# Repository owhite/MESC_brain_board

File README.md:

# Balancing Robot Design and Implementation

This repository is a structured set of lab notes and implementation records for developing a two-wheeled self-balancing robot. It documents the workflows from physical modeling and parameter measurement through firmware design, control implementation, and experimental validation.

The focus is on reproducibility and engineering rigor: measured motor parameters, deterministic control-loop behavior, system identification, control design tradeoffs, and verification testing are all captured alongside working code and experiments.

Topics covered include:
- Control design and validation workflows for balancing robots
- Motor parameter measurement (phase resistance, d/q inductance, damping)
- Deterministic embedded firmware structure for real-time control
- Encoder integration and signal integrity checks
- CAN communication and timing behavior
- Failure modes and debugging notes
- Practical test methods and instrumentation results

These notes are intended to make the development and validation process transparent and repeatable, not just to present final code.

## My balancing robot journey, specs and testing

* A subset of steps required to get a robot to stand [[LINK](DOCS/balancing_checklist.md)]
* Common issues that can break balancing in the brain board project [[LINK](DOCS/balancing_failures.md)]
* Firmware design choices that keep the balancing control loop deterministic [[LINK](DOCS/determinism_design.md)]
* Measuring phase resistance, d-axis, and q-axis inductance of a BLDC Motor [[LINK](DOCS/BLDC_inductance_measurement.md)]
* Dial in ChatGPT to be skeptical lab partner: [[LINK](DOCS/chatGPT_tips.md)]
* Development of the robot control board [[LINK](brainboardV1.2/README.md)]
* OTA programming [[LINK](RPI_OTA_BRIDGE/README.md)]
* Finalizing the modeling workflow [[LINK](modeling/README.md)]

## Not totally coherent discussions:
* [LQR](DOCS/learn_LQR.md). 
* Using the MT6701 [[LINK](DOCS/MT6701.md)] → works great but required some minor modifications to MESC position and [velocity measurement](DOCS/pos_vel_CAN.md)
* Measuring jitter on the MESC [[LINK](DOCS/jitter_testing.md)] → none found at current operating speeds
* Implementing CAN [[LINK](DOCS/CAN.md)]
* Notes about MESC [[LINK](DOCS/MESC_control_variables.md)]
* The inadequacies of PID [[LINK](DOCS/PID_position.md)]. 
* General description of firmware: [LINK](DOCS/teensy_firmware_walkthrough.md). 
* Brain board firmware [[LINK](DOCS/software_specs.md)]

## Laboratory notes, 2025

* [Position hold](DOCS/sept12_position_hold.md)
* [Controller issues](DOCS/sept18_controller_issues.md)
* [Torque nonlinearity](DOCS/sept19_torque_nonlinearity.md)
* [PID notes](DOCS/sept23_PID_notes.md)
* [Least squares](DOCS/sept30_least_squares.md)
* [Torque response](DOCS/oct03_torque_response.md)
* [LQR modeling](DOCS/oct11_LQR_modeling.md)
* [LQR height](DOCS/oct12_LQR_height.md)
* [IMU testing](DOCS/nov16_IMU.md)

## Let's be real

**You probably will not want to hear this.** If you came here for the code to make a balancing robot, it is here, but it probably wont help. 

You might assume building a balancing robot is mostly a matter of assembling parts and flashing someone else’s code onto it. I used to think that too — until I finally worked out how to create on one. Balancing robots are not just bolted together -- they are tuned and integrated. Everything about them depends on tight interactions between hardware, sensors, motors, and feedback loops, and those interactions are different for every single robot.

A balancing robot is a dynamic control system, not a static device. It’s constantly trying to predict its own motion, measure its own tilt, compensate for delays, cancel vibration, and stabilize itself against gravity — hundreds of times per second. That means even small differences in hardware completely change the way the controller behaves. For example:

- Motors & ESCs: Different torque curves, different dead zones, different current limits, different FOC tuning.
- Wheels & tires: Diameter, traction, inertia, compliance — all change how the robot responds to torque.
- IMU: Sensitivity, noise, mounting vibration, sample timing, bias drift — all affect measured tilt.
- Microcontroller timing: Loop rate, jitter, scheduling delays, filter performance — all shift the controller behavior.
- Physical build: Height of the center of mass, frame stiffness, mass distribution — all change the robot’s dynamics.

If you change any of these, even slightly, the controller behaves differently. That’s why tuning is so time-consuming: you’re adjusting a control law to match the physics and imperfections of your specific robot.

_You are welcome to take my code and run it on your bot._ But unfortunately just like musical instruments or high-performance cars, balancing robots need to be customized, adjusted, and dialed in until the system “feels right.” The code is just the beginning; the tuning is the craft.

Why? Well:
- Your robot will not balance without a lot of tuning.
- What's most important to use this project as a prompt for making your own system
- Tuning is the real work — not a flaw, but part of the fun
- What really makes a robot stand is eliminating all the problems like jitter, timing issues, CAN communications, and modeling

**Finally, dearest reader**... I care about you, youre adorable, but quite unfortunately one the PCB for one of the ESCs that I use is closed source. Nothing would delight me more to make it open and I will try. For a while, I was using the Flipsky Mini FSESC6.7 pro 70A but I got tired of blowing them up because of cheap parts. Some day I will make a balancing bot that runs on [moteus](https://mjbots.com/products/moteus-r4-11) or [odrive](https://odriverobotics.com) but right now that is not a priority. 

For these reasons and others you cant expect to use this repo to build a balancing robot like some sort of kit.

## The really great news is there is a new source of help. 

I want to be transparent about this: building a robot is not about writing code. I've written code for 20 plus years, in my case I worked through the entire project with ChatGPT as a kind of engineering partner. ChatG helps with asking questions, testing ideas, refining approaches, debugging weird behavior, and iterating the design over and over.

A balancing robot is a complex closed-loop control problem. As far as I know I never would have been able to use Google to address how robots behaves. ChatGPT creates the ability to explore those problems conversationally:

- When I wasn’t sure whether the IMU filtering was right, I asked it to analyze my data.
- It is incredible at helping with plotting results
- When I had motor vibration I couldn’t explain, I used chat to brainstorm possible causes and experiments.
- It taught me everything about LQR, interpretted equations, supplied python code to perform most of the calculations. It involved a lot of debugging -- when the LQR gains seemed wrong, I walked through the math with it.
- When the ESC behavior looked inconsistent, we debugged line by line until we understood it.
- When I needed to test an assumption, it helped me design the test.
- When something behaved strangely, I could describe it and get three possible hypotheses to try.
- ChatG is uncanny at image analysis. It reads part numbers off of chips and will take you to the spec sheet. Take a picture of a square wave of your scope - - the damn thing will tell you the frequency, amplitude of the wave. It also taught me how to set up [one-shot measurements](DOCS/BLDC_inductance_measurement.md). 

The project was far less like copying code from the internet and more like having a very patient senior engineer building one-off code bundles to eventually get this thing to stand. 

**We live in a world of prompt-driven engineering:** I shaped my thinking through prompts, refined those prompts based on the robot’s behavior, and used those conversations to build understanding that would have taken months on my own. ChatGPT didn’t “solve the problem” — it helped me reason through it, step by step.

So if you see this robot standing and balancing in a video, know that behind the scenes was not just hardware and code — it was hundreds of micro-conversations, experiments, adjustments, and iterations. ChatGPT was the scaffolding that helped me structure that process.

## ACKNOWLEDGEMENTS
This project would be completely impossible without the help, support and guidance of David Molony, developer of [MESC firmware](https://github.com/davidmolony/MESC_Firmware.git). Use of the MESC firmware is described throughout this repo.

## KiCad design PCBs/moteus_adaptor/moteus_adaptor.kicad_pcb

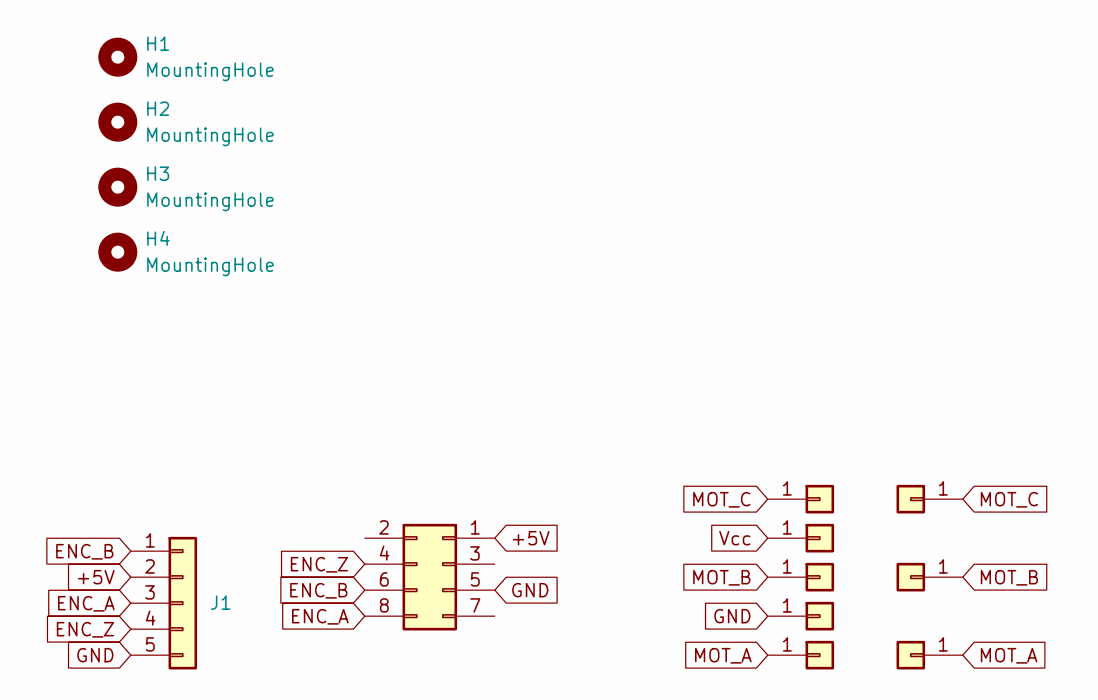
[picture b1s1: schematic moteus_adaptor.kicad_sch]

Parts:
H1, H2, H3, H4: MountingHole; MountingHole_2.5mm
J1: Conn_01x05; PinHeader_1x05_P2.54mm_Vertical
J2: Conn_02x04_Odd_Even; PinSocket_2x04_P1.27mm_Vertical
J3, J4, J5, J6, J7: Conn_01x01; my_Pin_D2.0mm
J8, J10, J12: Conn_01x01; my_Pin_D2.6mm

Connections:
+5V: J1.2, J2.1
ENC_A: J1.3, J2.8
ENC_B: J1.1, J2.6
ENC_Z: J1.4, J2.4
GND: J1.5, J2.5, J5.1
MOT_A: J6.1, J12.1
MOT_B: J4.1, J10.1
MOT_C: J7.1, J8.1
Vcc: J3.1

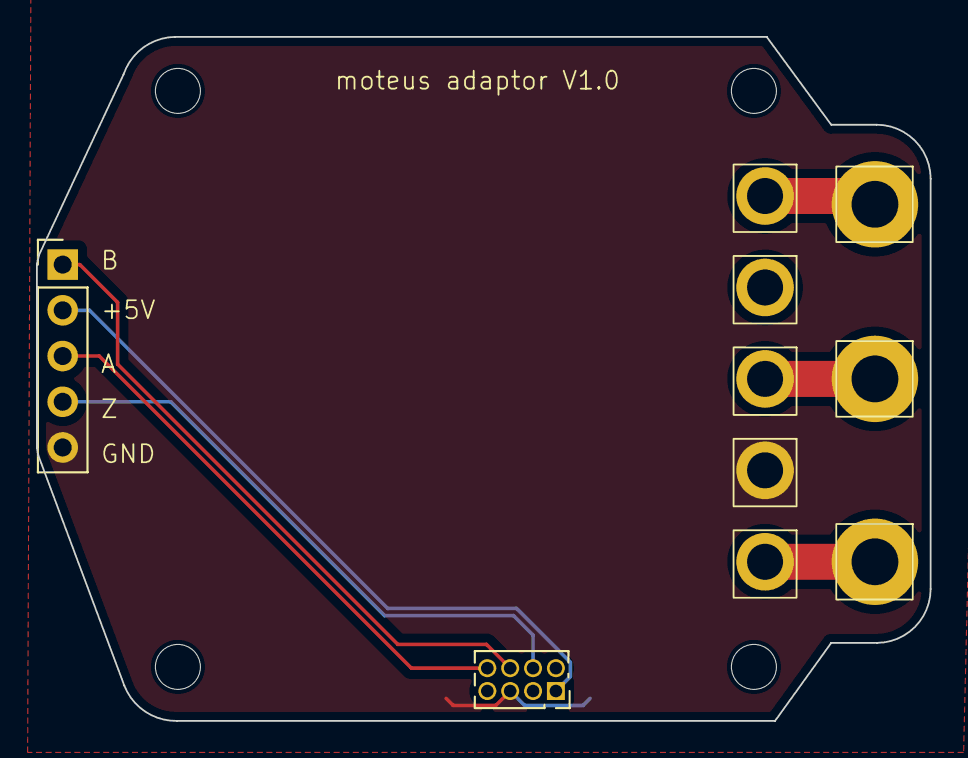
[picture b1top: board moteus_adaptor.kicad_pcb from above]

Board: 2 copper layers, 49.7 x 38.0 mm, 14 parts (0 on the bottom side), 8 nets.

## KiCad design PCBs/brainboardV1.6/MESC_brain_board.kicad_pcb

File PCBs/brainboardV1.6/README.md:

# MESC BRAIN BOARD 

A PCB and software development project for a balancing robot. 

The goal is to use a hobby Electronic Speed Controller (one open source [example](https://github.com/owhite/MP2-DFN), and this circuit for a [brain board](https://github.com/owhite/MESC_brain_board/blob/main/brainboardV1.0/MESC_brain_board.pdf), a teensy 4.0, and an ESP-32, in combination with [MESC firmware](https://github.com/davidmolony/MESC_Firmware).

## GENERAL APPROACH

A separation of concerns is divided across these architectures:

* **Teensy:** Runs the high-level brain → gait generator, balance estimator, RC inputs
* **MESC:** The firmware on the ESC for control → torque or velocity loops per joint
* **ESP32:** Easy to log and analyze later → pumps UDP to the computer
* **Desktop computer** → perfectly adequate way of viewing high speed data with UDP

## TEENSY 4.0
* 600+ MHz ARM Cortex-M7 — plenty of headroom for filtering, control loops, gait logic, telemetry
* Tons of I/O for IMU, encoders, RC input, WiFi (via ESP add-on), etc.
* Precise timing with elapsedMicros or interrupts for deterministic control
* Great for real-time control, sensor fusion, and behavior modeling

## MESC MOTOR CONTROLLER
* Deploys on simple DIY or commercially available ESC boards
* Executes low-level Field-Oriented Control (FOC) motor control 
* Built-in support for encoders, FOC, and torque estimation
* Accurate low-level motor control using current sensing
* Reads angular position from the MT6701 encoder via SPI or PWM
* UART/CAN interface (RX + TX)	Real-time communication with the Teensy
* PWM / FOC commutation w/ efficient, smooth motor operation

## OTHER BRAIN BOARD FEATURES
* RC receiver connector (for PWM/PPM/SBUS input)
* ESP32 UART serial programmer
* Power input connector
* Voltage divider (to monitor battery voltage)
* Push-button E-stop connector
* Power button (for system on/off)
* IMU connector (e.g., MPU-6050)
* Buzzer (for system alerts or E-stop signal)
* MESC I/O
* Reserved 2 GPIO pins on Teensy for emergency shutoff to MESC
* CAN connector (for MESC motor control)

## CAN BUS
* Full-duplex communication between Teensy and motor controllers
* Carries:
  * Commands: set_torque, set_velocity, enable_motor, zero_encoder, etc.
  * Telemetry: encoder position, estimated torque, velocity, fault codes
* Real-time performance with minimal latency
* Can support multiple motor controllers on the same bus

## MANY THANKS
This project would never happen without:
* [MESC firmware](https://github.com/davidmolony/MESC_Firmware). 
* [Netzpfuscher's](https://github.com/Netzpfuscher/TTerm) incredible TTerm and CAN work.
* [MP2](https://github.com/badgineer/MP2-ESC) an open source motor controller from badgineer. 

## NOTES
Ever wanted to change all the names of kicad files at once?

use this:
```
python3 replace_kicad_names.py VESC_brain_board MESC_brain_board
```

[[LINK](replace_kicad_names.py)]

## STILL NEEDS WORK
* Not great design w/ DC-DC conversion from high voltage VBat
* Replace out the IMU for a ICM-42688-P
* Order / revise pushbuttons for programming the ESP32
* Ensure 3.3V CAN transciever

## VERSIONS
* See github tag [pcb-v1](https://github.com/owhite/MESC_brain_board/releases/tag/pcb-v1) for V1.0
* Retreive with this command: "git checkout pcb-v1"

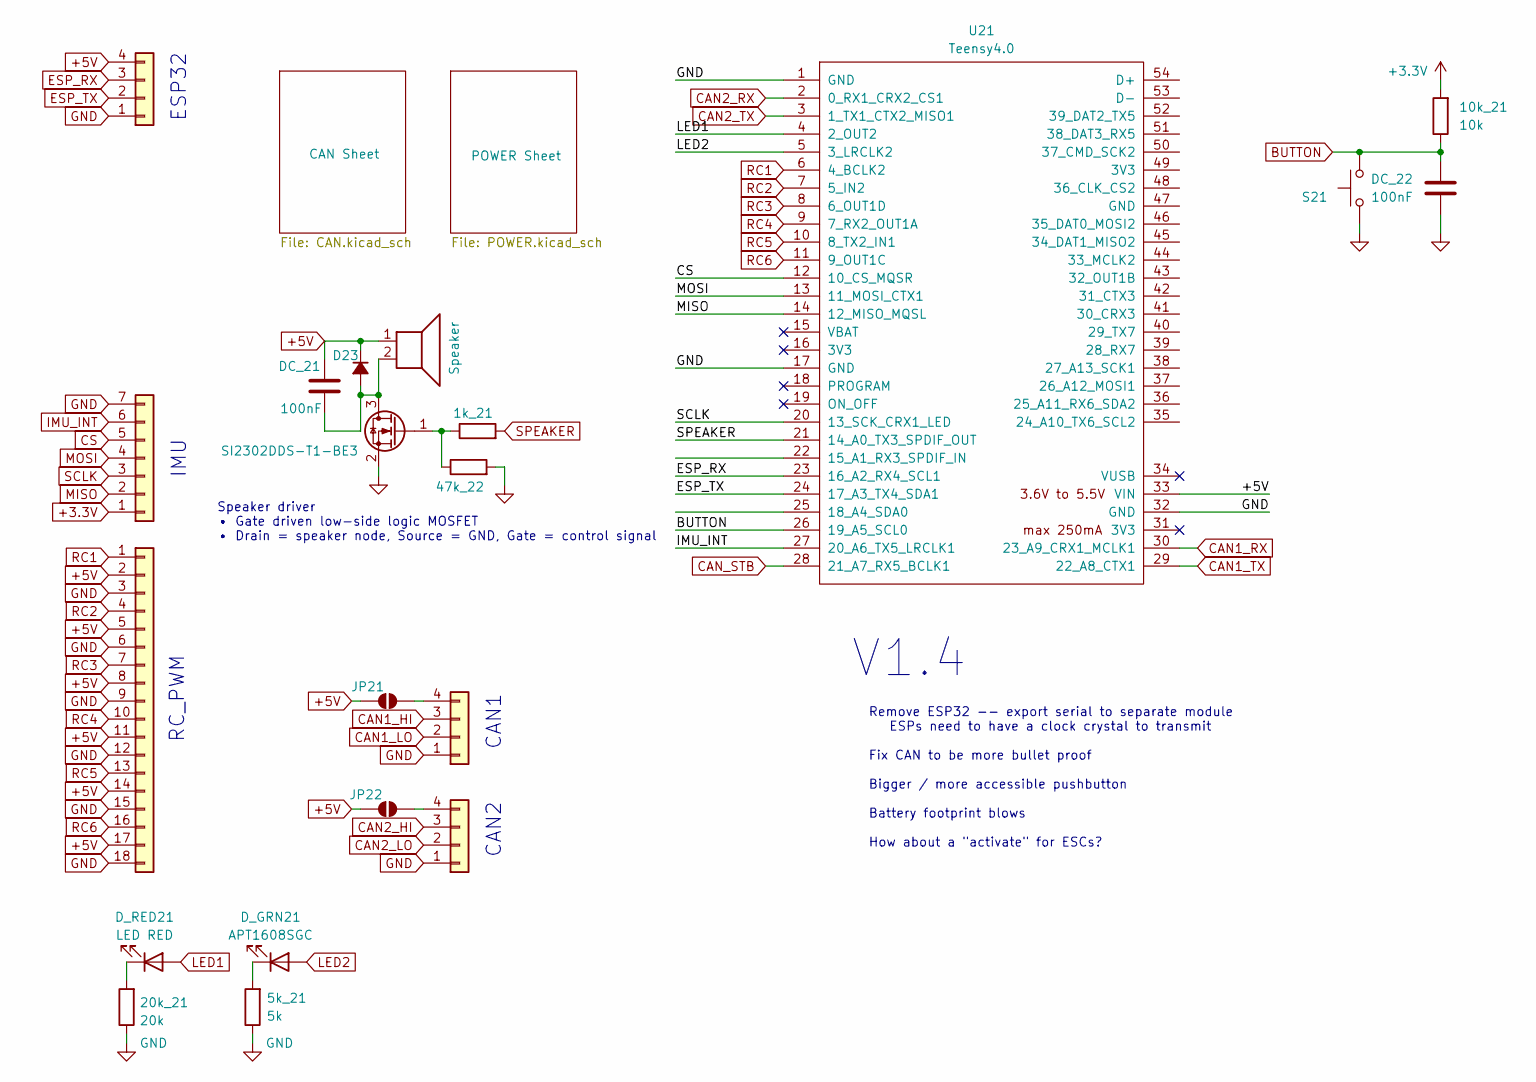
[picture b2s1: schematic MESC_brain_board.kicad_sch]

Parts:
1k_21, 47k_22: 10k; R_0603_1608Metric
5k_21: 5k; R_0603_1608Metric; LCSC C4184
10k_21: 10k; R_0603_1608Metric; LCSC C25804
20k_21: 20k; R_0603_1608Metric; LCSC C4184
CAN1, CAN2: Conn_01x04; JST_PH_B4B-PH-K_1x04_P2.00mm_Vertical
D23: D_Small_Filled; D_SMA
DC_21: 100nF; C_0603_1608Metric
DC_22: 100nF; C_0603_1608Metric; LCSC C14663
D_GRN21: APT1608SGC; LED_0603_1608Metric; LCSC APT1608SGC
D_RED21: LED RED; LED_0603_1608Metric; LCSC APT1608SURCK
ESP1: Conn_01x04; JST_PH_B4B-PH-K_1x04_P2.00mm_Vertical
IMU1: Conn_01x07; JST_PH_B7B-PH-K_1x07_P2.00mm_Vertical
J2: Conn_01x18; my_PinSocket_3x07_P2.54mm_Vertical
JP21, JP22: SolderJumper_2_Open; SolderJumper-2_P1.3mm_Open_RoundedPad1.0x1.5mm
LS21: Speaker; SPKR_CDS-13138-SMT-TR
Q21: SI2302DDS-T1-BE3; SOT-23
S21: TL1015AF160QG; SW_Push_SPST_NO_Alps_SKRK
U21: Teensy4.0; Teensy40

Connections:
+3.3V: 10k_21.2, IMU1.1; also elsewhere on the board
+5V: D23.1 (K), DC_21.1, ESP1.4, J2.2, J2.5, J2.8, J2.11, J2.14, J2.17, JP21.1 (A), JP22.1 (A), LS21.1, U21.33 (VIN); also elsewhere on the board
BUTTON: 10k_21.1, DC_22.2, S21.2, U21.26 (19_A5_SCL0)
CAN1_HI: CAN1.3; also elsewhere on the board
CAN1_LO: CAN1.2; also elsewhere on the board
CAN1_RX: U21.30 (23_A9_CRX1_MCLK1); also elsewhere on the board
CAN1_TX: U21.29 (22_A8_CTX1); also elsewhere on the board
CAN2_HI: CAN2.3; also elsewhere on the board
CAN2_LO: CAN2.2; also elsewhere on the board
CAN2_RX: U21.2 (0_RX1_CRX2_CS1); also elsewhere on the board
CAN2_TX: U21.3 (1_TX1_CTX2_MISO1); also elsewhere on the board
CAN_STB: U21.28 (21_A7_RX5_BCLK1); also elsewhere on the board
CS: IMU1.5, U21.12 (10_CS_MQSR)
ESP_RX: ESP1.3, U21.23 (16_A2_RX4_SCL1)
ESP_TX: ESP1.2, U21.24 (17_A3_TX4_SDA1)
GND: 5k_21.1, 20k_21.1, 47k_22.2, CAN1.1, CAN2.1, DC_22.1, ESP1.1, IMU1.7, J2.3, J2.6, J2.9, J2.12, J2.15, J2.18, Q21.2 (S), S21.1, U21.1 (GND), U21.17 (GND), U21.32 (GND); also elsewhere on the board
IMU_INT: IMU1.6, U21.27 (20_A6_TX5_LRCLK1)
LED1: D_RED21.2 (A), U21.4 (2_OUT2)
LED2: D_GRN21.2 (A), U21.5 (3_LRCLK2)
MISO: IMU1.2, U21.14 (12_MISO_MQSL)
MOSI: IMU1.4, U21.13 (11_MOSI_CTX1)
unnamed: CAN1.4, JP21.2 (B)
unnamed: CAN2.4, JP22.2 (B)
unnamed: D23.2 (A), DC_21.2, LS21.2, Q21.3 (D)
unnamed: 5k_21.2, D_GRN21.1 (K)
unnamed: 20k_21.2, D_RED21.1 (K)
unnamed: 1k_21.1, 47k_22.1, Q21.1 (G)
RC1: J2.1, U21.6 (4_BCLK2)
RC2: J2.4, U21.7 (5_IN2)
RC3: J2.7, U21.8 (6_OUT1D)
RC4: J2.10, U21.9 (7_RX2_OUT1A)
RC5: J2.13, U21.10 (8_TX2_IN1)
RC6: J2.16, U21.11 (9_OUT1C)
SCLK: IMU1.3, U21.20 (13_SCK_CRX1_LED)
SPEAKER: 1k_21.2, U21.21 (14_A0_TX3_SPDIF_OUT)

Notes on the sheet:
CAN2
IMU
V1.4
RC_PWM
Remove ESP32 -- export serial to separate module ESPs need to have a clock crystal to transmit Fix CAN to be more bullet proof Bigger / more accessible pushbutton Battery footprint blows How about a "activate" for ESCs?
Speaker driver • Gate driven low-side logic MOSFET • Drain = speaker node, Source = GND, Gate = control signal
CAN1
ESP32

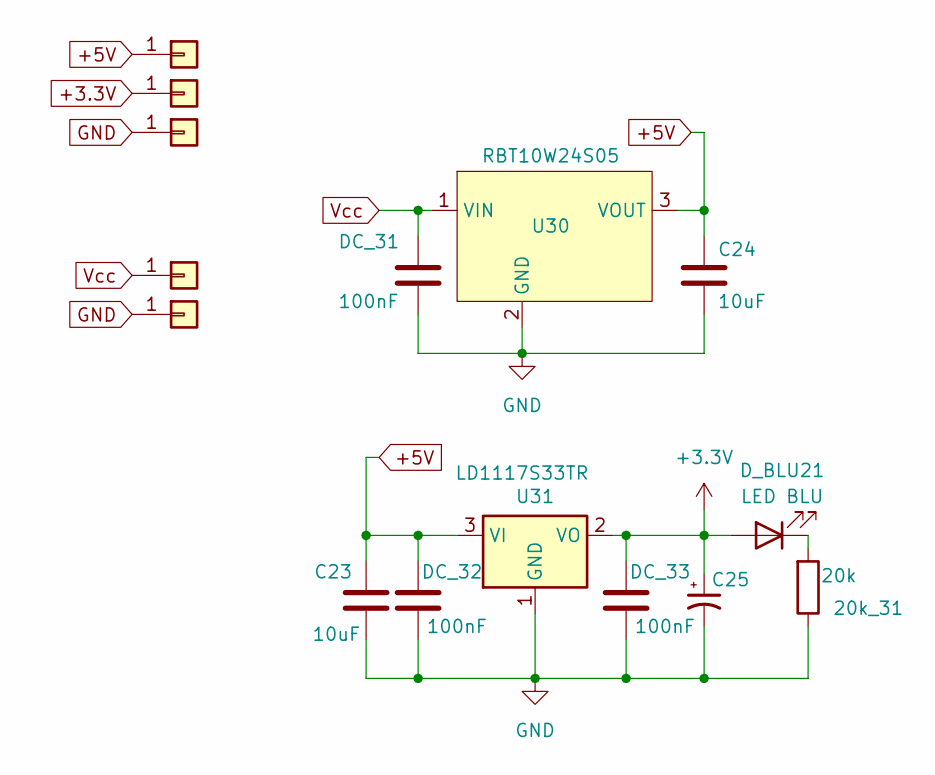
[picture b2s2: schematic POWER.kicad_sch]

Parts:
20k_31: 20k; R_0603_1608Metric; LCSC C4184
C23, C24: 10uF; C_0805_2012Metric; LCSC C96446
C25: T491A106K006AT; CP_EIA-3216-18_Kemet-A; LCSC C7171
DC_31, DC_32, DC_33: 100nF; C_0805_2012Metric; LCSC C342865
D_BLU21: LED BLU; LED_0603_1608Metric; LCSC APT1608QBC/D
J21, J22, J23: Conn_01x01; PinSocket_1x01_P2.54mm_Vertical
J24, J25: Conn_01x01; SolderWire-2sqmm_1x01_D2mm_OD3.9mm
U30: RBT10W24S05; 12_DCDC_5
U31: LD1117S33TR; SOT-223-3_TabPin2

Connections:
+3.3V: C25.1, DC_33.1, D_BLU21.2 (A), J23.1, U31.2 (VO); also elsewhere on the board
+5V: C23.1, C24.1, DC_32.1, J22.1, U30.3 (VOUT), U31.3 (VI); also elsewhere on the board
GND: 20k_31.1, C23.2, C24.2, C25.2, DC_31.2, DC_32.2, DC_33.2, J21.1, J25.1, U30.2 (GND), U31.1 (GND); also elsewhere on the board
unnamed: 20k_31.2, D_BLU21.1 (K)
Vcc: DC_31.1, J24.1, U30.1 (VIN)

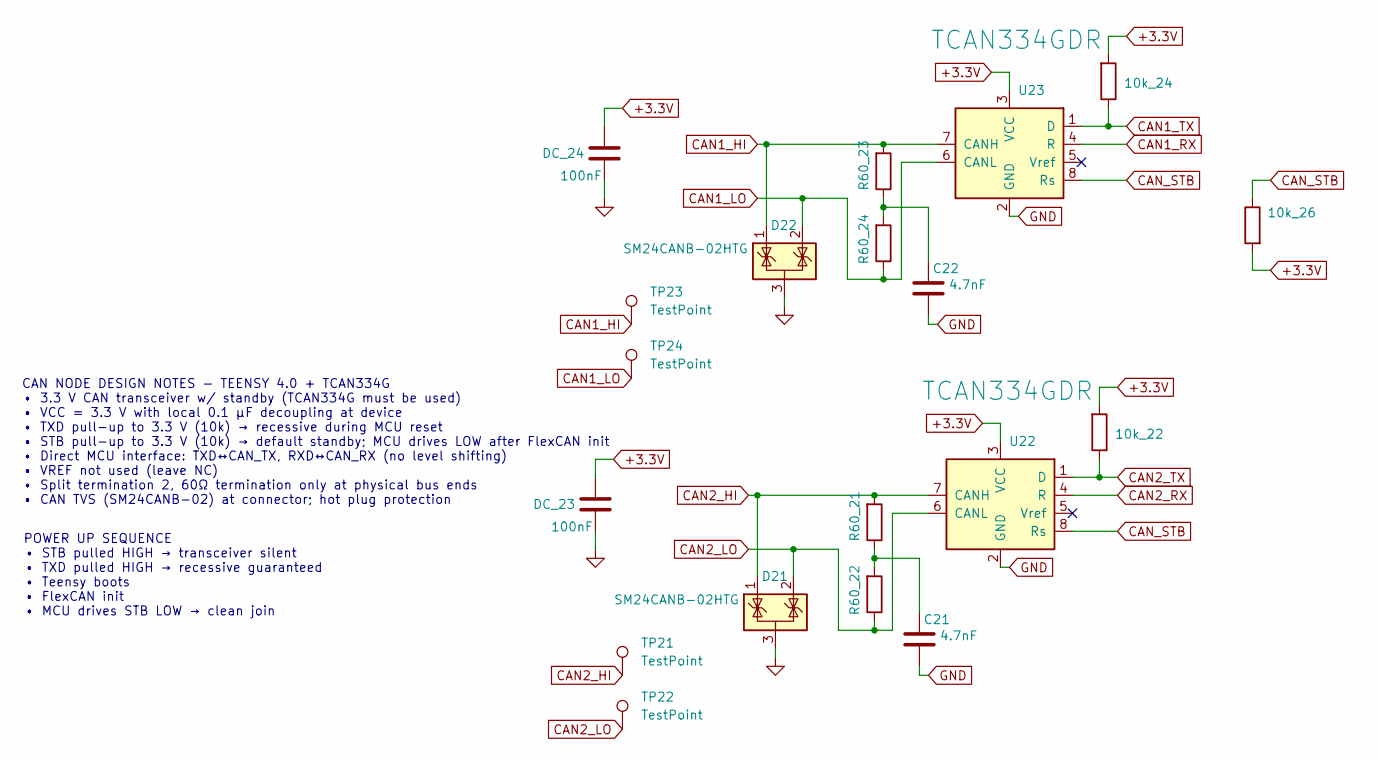
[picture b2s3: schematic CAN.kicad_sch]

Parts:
10k_22, 10k_24, 10k_26: 10k; R_0603_1608Metric; LCSC C25804
C21, C22: 4.7nF; C_0603_1608Metric
D21, D22: SM24CANB-02HTG; SOT95P230X117-3N
DC_23, DC_24: 100nF; C_0603_1608Metric
R60_21, R60_22, R60_23, R60_24: 60; R_0603_1608Metric; LCSC C17437
TP21, TP22, TP23, TP24: TestPoint; PinSocket_1x01_P2.54mm_Vertical
U22, U23: TCAN334GDR; SOIC-8_3.9x4.9mm_P1.27mm; LCSC C6952

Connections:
+3.3V: 10k_22.2, 10k_24.2, 10k_26.2, DC_23.1, DC_24.1, U22.3 (VCC), U23.3 (VCC); also elsewhere on the board
CAN1_HI: D22.1 (K), R60_23.2, TP23.1, U23.7 (CANH); also elsewhere on the board
CAN1_LO: D22.2 (K), R60_24.1, TP24.1, U23.6 (CANL); also elsewhere on the board
CAN1_RX: U23.4 (R); also elsewhere on the board
CAN1_TX: 10k_24.1, U23.1 (D); also elsewhere on the board
CAN2_HI: D21.1 (K), R60_21.2, TP21.1, U22.7 (CANH); also elsewhere on the board
CAN2_LO: D21.2 (K), R60_22.1, TP22.1, U22.6 (CANL); also elsewhere on the board
CAN2_RX: U22.4 (R); also elsewhere on the board
CAN2_TX: 10k_22.1, U22.1 (D); also elsewhere on the board
CAN_STB: 10k_26.1, U22.8 (Rs), U23.8 (Rs); also elsewhere on the board
GND: C21.2, C22.2, D21.3 (A), D22.3 (A), DC_23.2, DC_24.2, U22.2 (GND), U23.2 (GND); also elsewhere on the board
unnamed: C21.1, R60_21.1, R60_22.2
unnamed: C22.1, R60_23.1, R60_24.2

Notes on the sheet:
CAN NODE DESIGN NOTES - TEENSY 4.0 + TCAN334G • 3.3 V CAN transceiver w/ standby (TCAN334G must be used) • VCC = 3.3 V with local 0.1 µF decoupling at device • TXD pull-up to 3.3 V (10k) → recessive during MCU reset • STB pull-up to 3.3 V (10k) → default standby; MCU drives LOW after FlexCAN init •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
POWER UP SEQUENCE • STB pulled HIGH → transceiver silent • TXD pulled HIGH → recessive guaranteed • Teensy boots • FlexCAN init • MCU drives STB LOW → clean join

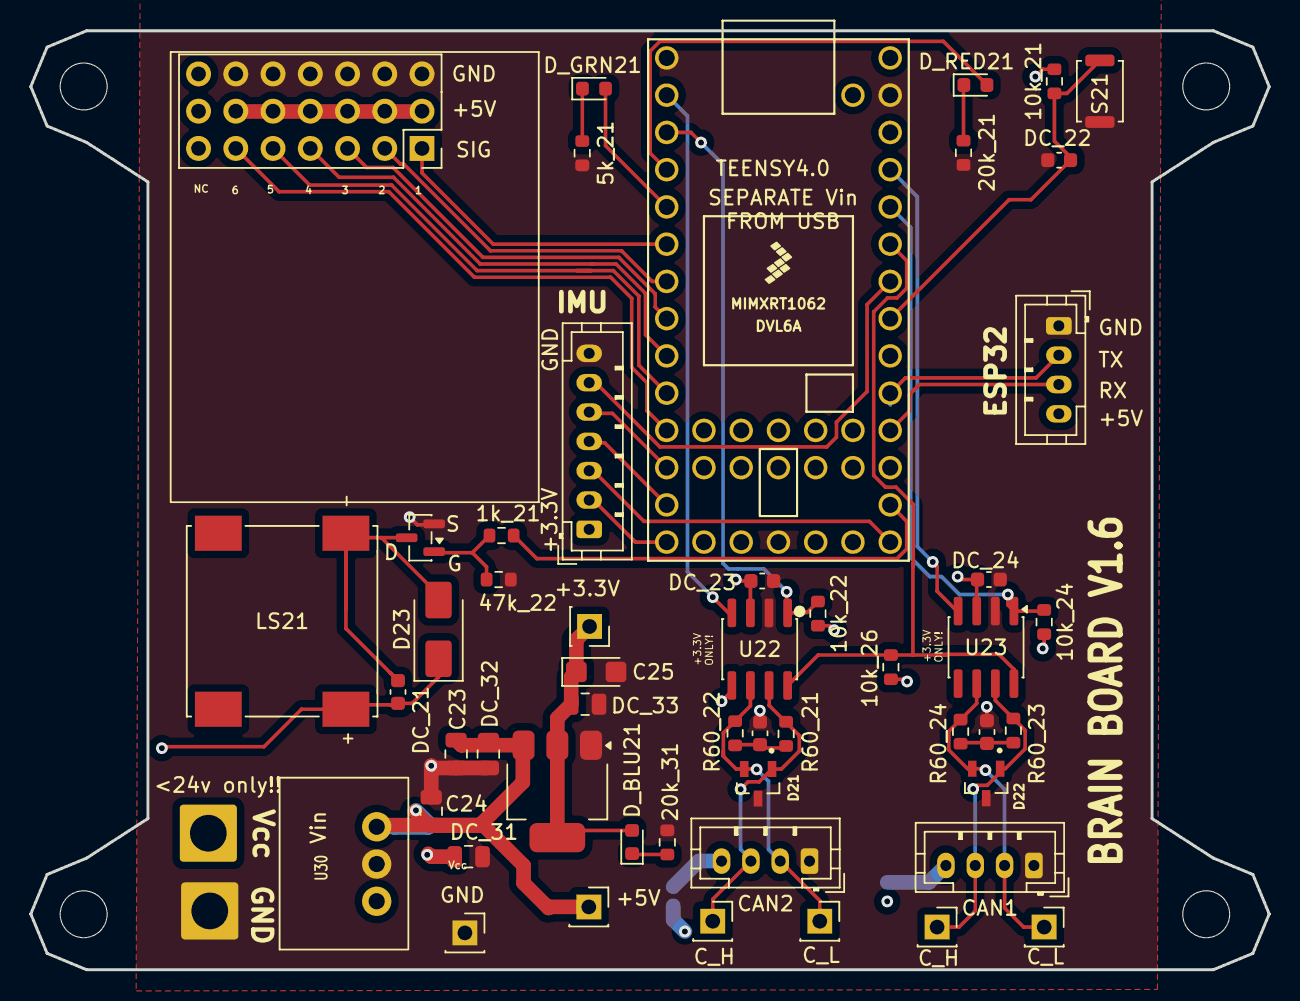
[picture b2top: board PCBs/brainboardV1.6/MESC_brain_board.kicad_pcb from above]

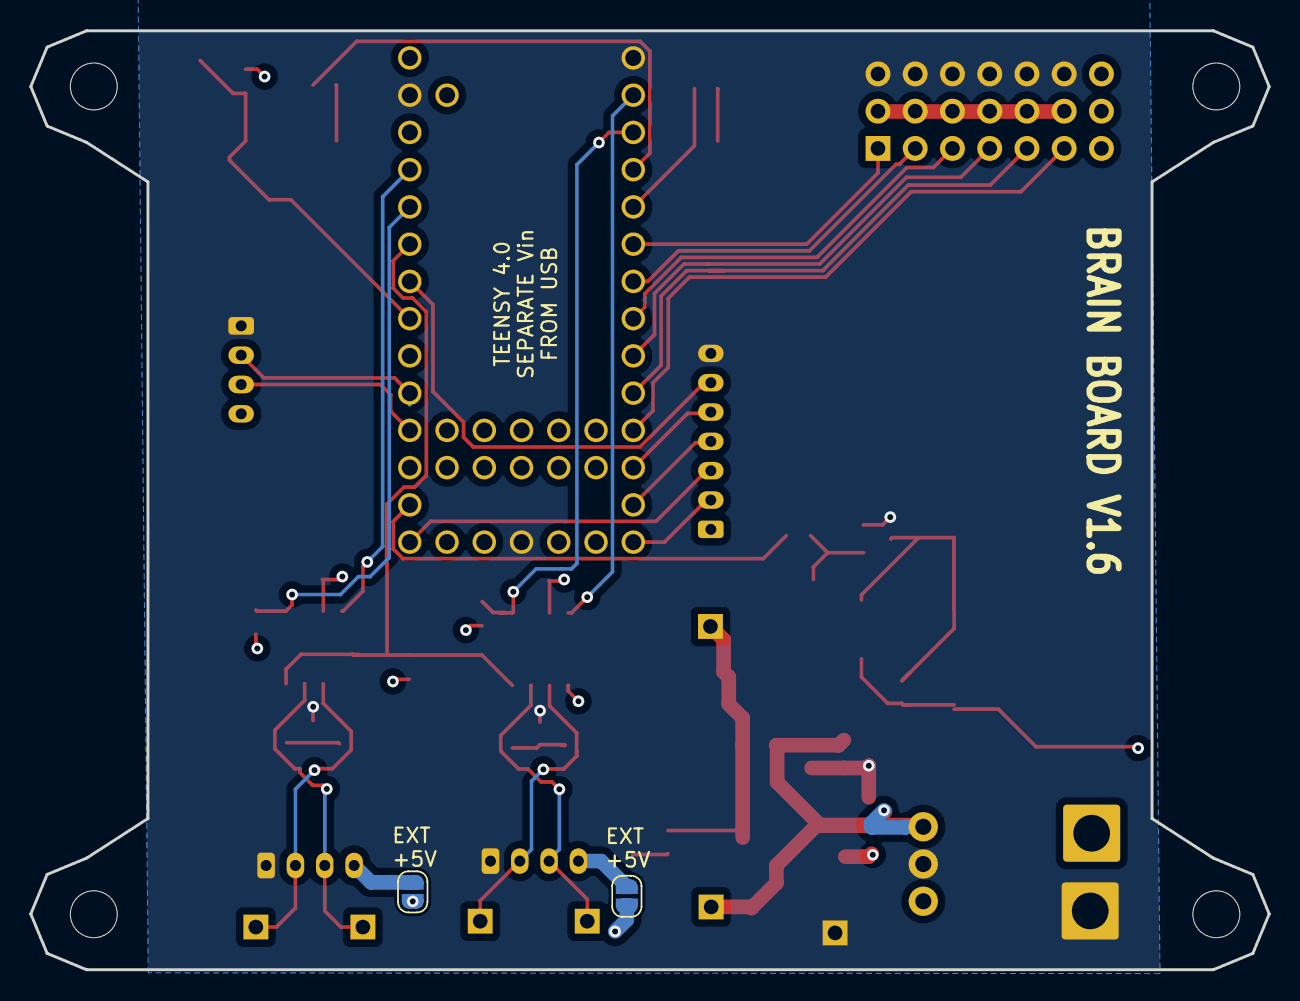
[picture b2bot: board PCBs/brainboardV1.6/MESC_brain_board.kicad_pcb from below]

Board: 4 copper layers, 84.5 x 64.0 mm, 55 parts (2 on the bottom side), 39 nets.

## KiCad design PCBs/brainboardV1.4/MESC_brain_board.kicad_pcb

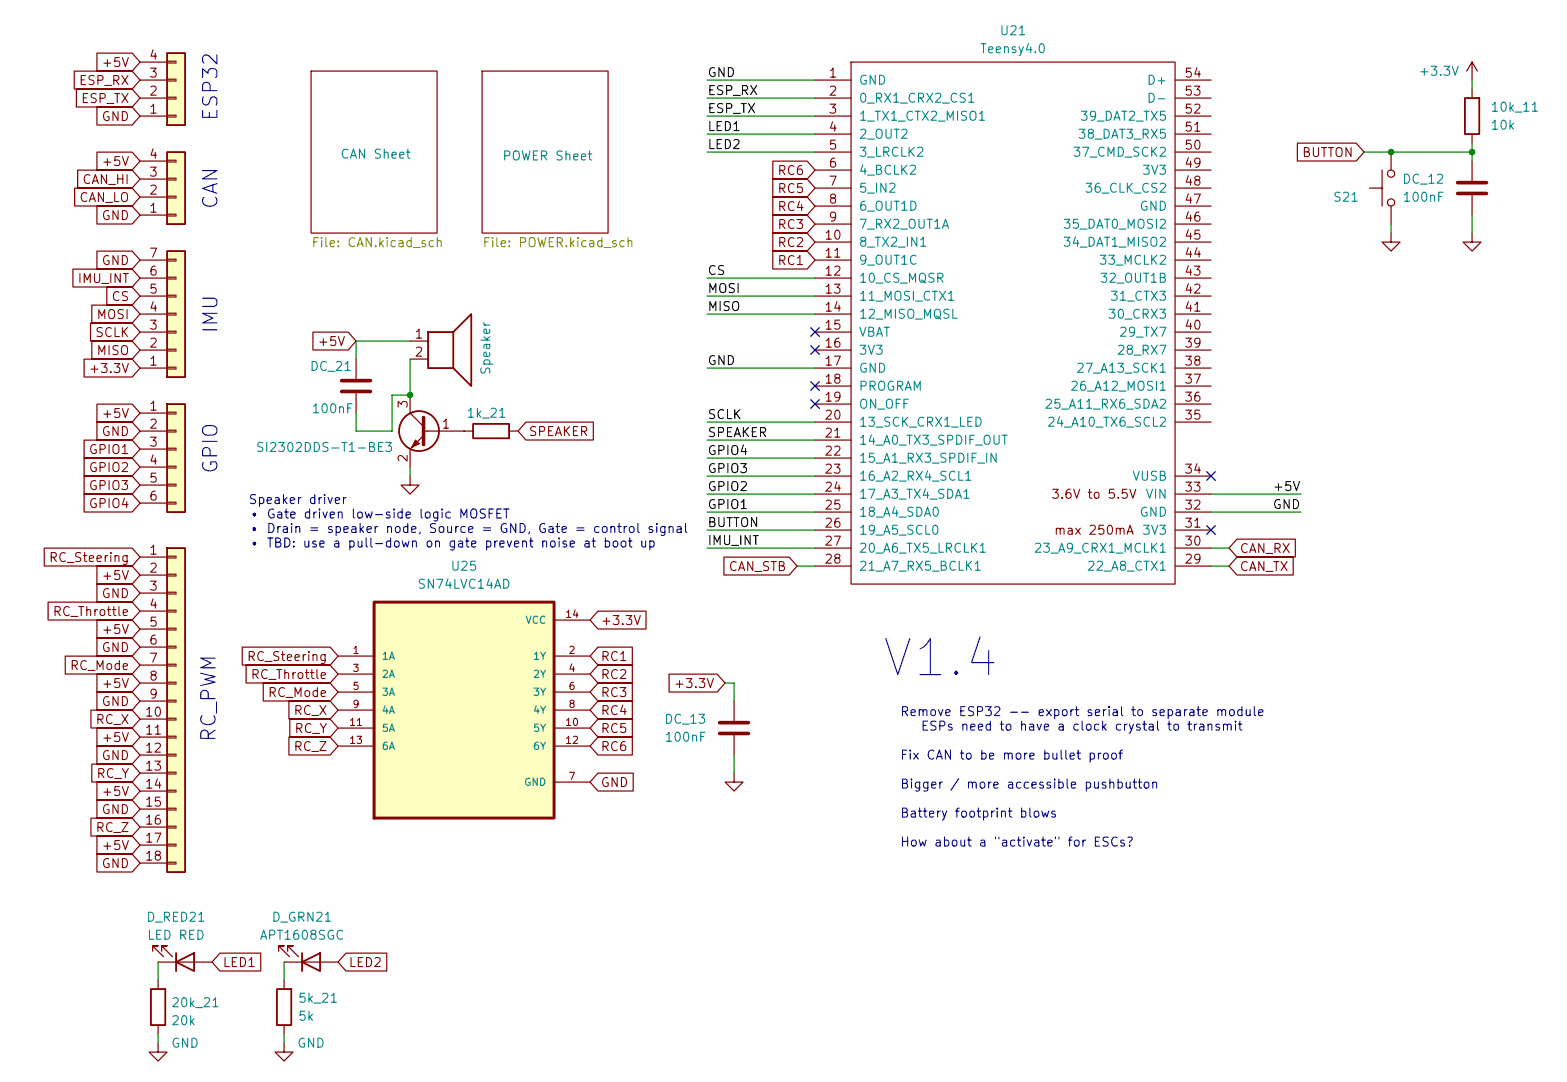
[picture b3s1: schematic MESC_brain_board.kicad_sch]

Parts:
1k_21: 10k; R_0603_1608Metric
5k_21: 5k; R_0603_1608Metric; LCSC C4184
10k_11: 10k; R_0603_1608Metric; LCSC C25804
20k_21: 20k; R_0603_1608Metric; LCSC C4184
CAN1: Conn_01x04; JST_PH_B4B-PH-K_1x04_P2.00mm_Vertical
DC_12, DC_13: 100nF; C_0603_1608Metric; LCSC C14663
DC_21: 100nF; C_0603_1608Metric
D_GRN21: APT1608SGC; LED_0603_1608Metric; LCSC APT1608SGC
D_RED21: LED RED; LED_0603_1608Metric; LCSC APT1608SURCK
ESP1: Conn_01x04; JST_PH_B4B-PH-K_1x04_P2.00mm_Vertical
GPIO1: Conn_01x06; JST_PH_B6B-PH-K_1x06_P2.00mm_Vertical
IMU1: Conn_01x07; JST_PH_B7B-PH-K_1x07_P2.00mm_Vertical
J1: Conn_01x18; my_PinSocket_3x07_P2.54mm_Vertical
LS21: Speaker; SPKR_CDS-13138-SMT-TR
Q1: SI2302DDS-T1-BE3; SOT-23
S21: TL1015AF160QG; SW_Push_SPST_NO_Alps_SKRK
U21: Teensy4.0; Teensy40
U25: SN74LVC14AD; SOIC127P600X175-14N

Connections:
+3.3V: 10k_11.2, DC_13.2, IMU1.1, U25.14 (VCC); also elsewhere on the board
+5V: CAN1.4, DC_21.1, ESP1.4, GPIO1.1, J1.2, J1.5, J1.8, J1.11, J1.14, J1.17, LS21.1, U21.33 (VIN); also elsewhere on the board
BUTTON: 10k_11.1, DC_12.2, S21.2, U21.26 (19_A5_SCL0)
CAN_HI: CAN1.3; also elsewhere on the board
CAN_LO: CAN1.2; also elsewhere on the board
CAN_RX: U21.30 (23_A9_CRX1_MCLK1); also elsewhere on the board
CAN_STB: U21.28 (21_A7_RX5_BCLK1); also elsewhere on the board
CAN_TX: U21.29 (22_A8_CTX1); also elsewhere on the board
CS: IMU1.5, U21.12 (10_CS_MQSR)
ESP_RX: ESP1.3, U21.2 (0_RX1_CRX2_CS1)
ESP_TX: ESP1.2, U21.3 (1_TX1_CTX2_MISO1)
GND: 5k_21.1, 20k_21.1, CAN1.1, DC_12.1, DC_13.1, ESP1.1, GPIO1.2, IMU1.7, J1.3, J1.6, J1.9, J1.12, J1.15, J1.18, Q1.2 (E), S21.1, U21.1 (GND), U21.17 (GND), U21.32 (GND), U25.7 (GND); also elsewhere on the board
GPIO1: GPIO1.3, U21.25 (18_A4_SDA0)
GPIO2: GPIO1.4, U21.24 (17_A3_TX4_SDA1)
GPIO3: GPIO1.5, U21.23 (16_A2_RX4_SCL1)
GPIO4: GPIO1.6, U21.22 (15_A1_RX3_SPDIF_IN)
IMU_INT: IMU1.6, U21.27 (20_A6_TX5_LRCLK1)
LED1: D_RED21.2 (A), U21.4 (2_OUT2)
LED2: D_GRN21.2 (A), U21.5 (3_LRCLK2)
MISO: IMU1.2, U21.14 (12_MISO_MQSL)
MOSI: IMU1.4, U21.13 (11_MOSI_CTX1)
unnamed: 5k_21.2, D_GRN21.1 (K)
unnamed: 20k_21.2, D_RED21.1 (K)
unnamed: 1k_21.1, Q1.1 (B)
unnamed: DC_21.2, LS21.2, Q1.3 (C)
RC1: U21.11 (9_OUT1C), U25.2 (1Y)
RC2: U21.10 (8_TX2_IN1), U25.4 (2Y)
RC3: U21.9 (7_RX2_OUT1A), U25.6 (3Y)
RC4: U21.8 (6_OUT1D), U25.8 (4Y)
RC5: U21.7 (5_IN2), U25.10 (5Y)
RC6: U21.6 (4_BCLK2), U25.12 (6Y)
RC_Mode: J1.7, U25.5 (3A)
RC_Steering: J1.1, U25.1 (1A)
RC_Throttle: J1.4, U25.3 (2A)
RC_X: J1.10, U25.9 (4A)
RC_Y: J1.13, U25.11 (5A)
RC_Z: J1.16, U25.13 (6A)
SCLK: IMU1.3, U21.20 (13_SCK_CRX1_LED)
SPEAKER: 1k_21.2, U21.21 (14_A0_TX3_SPDIF_OUT)

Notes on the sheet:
IMU
V1.4
GPIO
RC_PWM
Remove ESP32 -- export serial to separate module ESPs need to have a clock crystal to transmit Fix CAN to be more bullet proof Bigger / more accessible pushbutton Battery footprint blows How about a "activate" for ESCs?
Speaker driver • Gate driven low-side logic MOSFET • Drain = speaker node, Source = GND, Gate = control signal • TBD: use a pull-down on gate prevent noise at boot up
CAN
ESP32

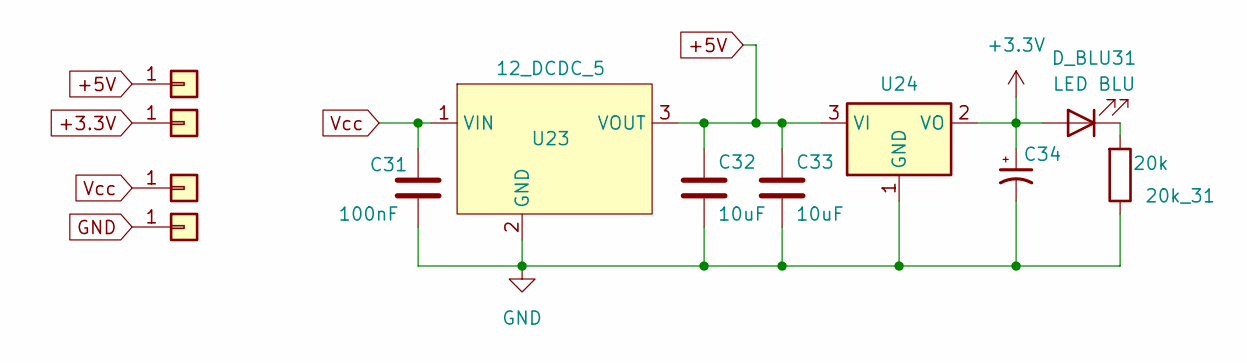
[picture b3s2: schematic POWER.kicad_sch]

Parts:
20k_31: 20k; R_0603_1608Metric; LCSC C4184
C31: 100nF; C_0805_2012Metric; LCSC C342865
C32, C33: 10uF; C_0805_2012Metric; LCSC C96446
C34: C_Polarized_Small_US; CP_EIA-3216-18_Kemet-A; LCSC C7171
D_BLU31: LED BLU; LED_0603_1608Metric; LCSC APT1608QBC/D
J23, J24: Conn_01x01; PinSocket_1x01_P2.54mm_Vertical
J25, J26: Conn_01x01; SolderWire-2sqmm_1x01_D2mm_OD3.9mm
U23: 12_DCDC_5
U24: LD1117S18TR_SOT223; SOT-223-3_TabPin2; LCSC C2984862

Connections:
+3.3V: C34.1, D_BLU31.2 (A), J24.1, U24.2 (VO); also elsewhere on the board
+5V: C32.1, C33.1, J23.1, U23.3 (VOUT), U24.3 (VI); also elsewhere on the board
GND: 20k_31.1, C31.2, C32.2, C33.2, C34.2, J26.1, U23.2 (GND), U24.1 (GND); also elsewhere on the board
unnamed: 20k_31.2, D_BLU31.1 (K)
Vcc: C31.1, J25.1, U23.1 (VIN)

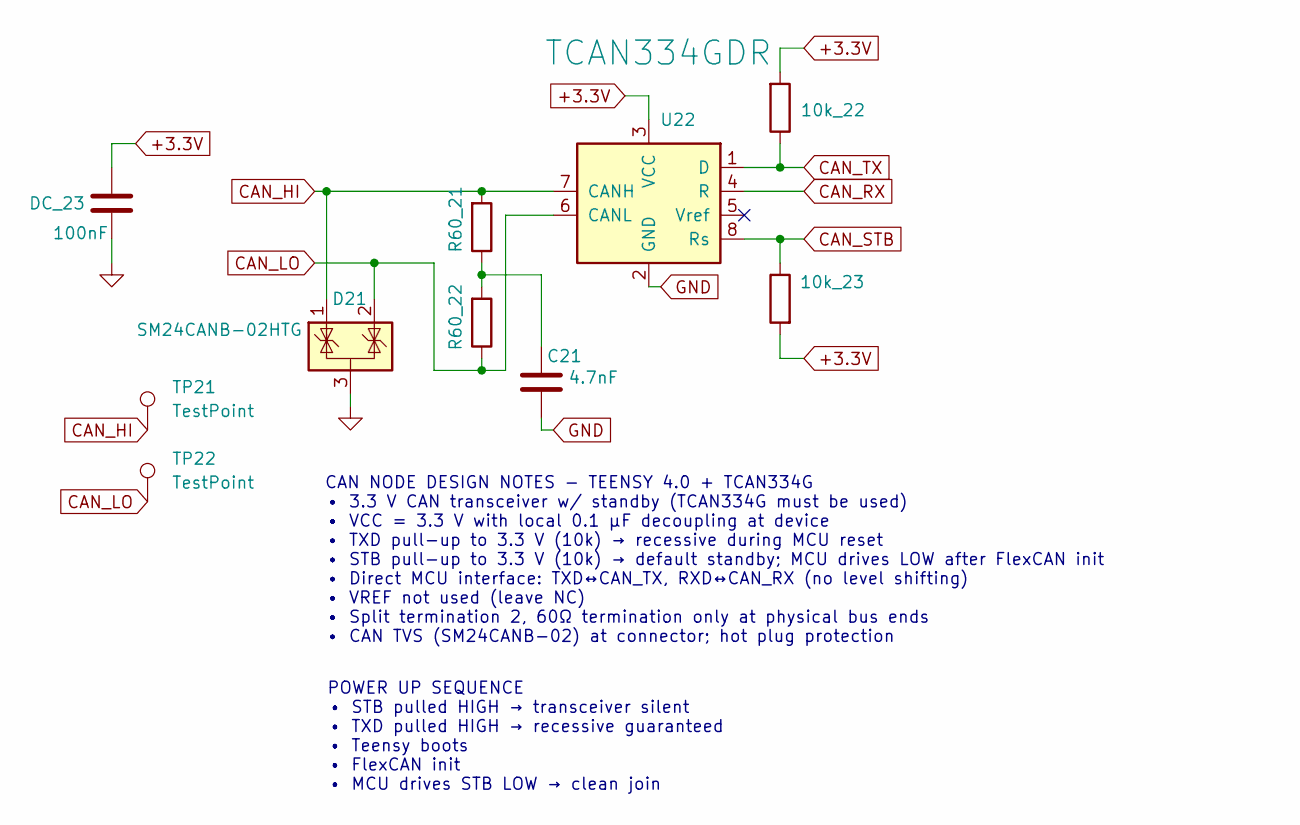
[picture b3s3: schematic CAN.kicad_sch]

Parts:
10k_22, 10k_23: 10k; R_0603_1608Metric; LCSC C25804
C21: 4.7nF; C_0603_1608Metric
D21: SM24CANB-02HTG; SOT95P230X117-3N
DC_23: 100nF; C_0603_1608Metric
R60_21, R60_22: 60; R_0603_1608Metric; LCSC C17437
TP21, TP22: TestPoint; PinSocket_1x01_P2.54mm_Vertical
U22: TCAN334GDR; SOIC-8_3.9x4.9mm_P1.27mm; LCSC C6952

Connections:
+3.3V: 10k_22.2, 10k_23.2, DC_23.1, U22.3 (VCC); also elsewhere on the board
CAN_HI: D21.1 (K), R60_21.2, TP21.1, U22.7 (CANH); also elsewhere on the board
CAN_LO: D21.2 (K), R60_22.1, TP22.1, U22.6 (CANL); also elsewhere on the board
CAN_RX: U22.4 (R); also elsewhere on the board
CAN_STB: 10k_23.1, U22.8 (Rs); also elsewhere on the board
CAN_TX: 10k_22.1, U22.1 (D); also elsewhere on the board
GND: C21.2, D21.3 (A), DC_23.2, U22.2 (GND); also elsewhere on the board
unnamed: C21.1, R60_21.1, R60_22.2

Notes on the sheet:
CAN NODE DESIGN NOTES - TEENSY 4.0 + TCAN334G • 3.3 V CAN transceiver w/ standby (TCAN334G must be used) • VCC = 3.3 V with local 0.1 µF decoupling at device • TXD pull-up to 3.3 V (10k) → recessive during MCU reset • STB pull-up to 3.3 V (10k) → default standby; MCU drives LOW after FlexCAN init •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
POWER UP SEQUENCE • STB pulled HIGH → transceiver silent • TXD pulled HIGH → recessive guaranteed • Teensy boots • FlexCAN init • MCU drives STB LOW → clean join

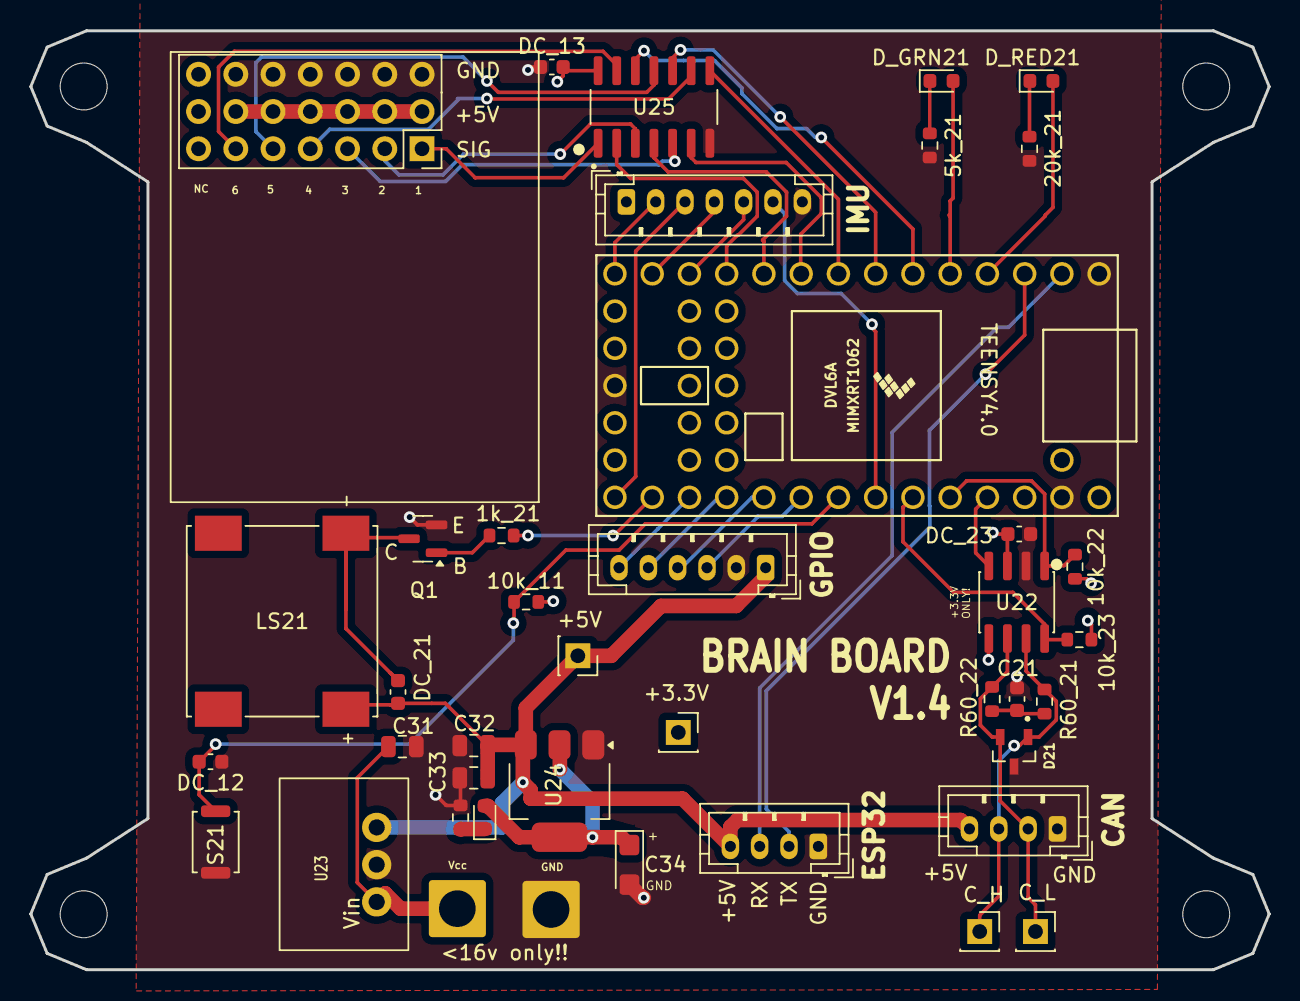
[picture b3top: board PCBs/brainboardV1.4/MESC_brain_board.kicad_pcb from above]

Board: 4 copper layers, 84.5 x 64.0 mm, 41 parts (0 on the bottom side), 42 nets.
